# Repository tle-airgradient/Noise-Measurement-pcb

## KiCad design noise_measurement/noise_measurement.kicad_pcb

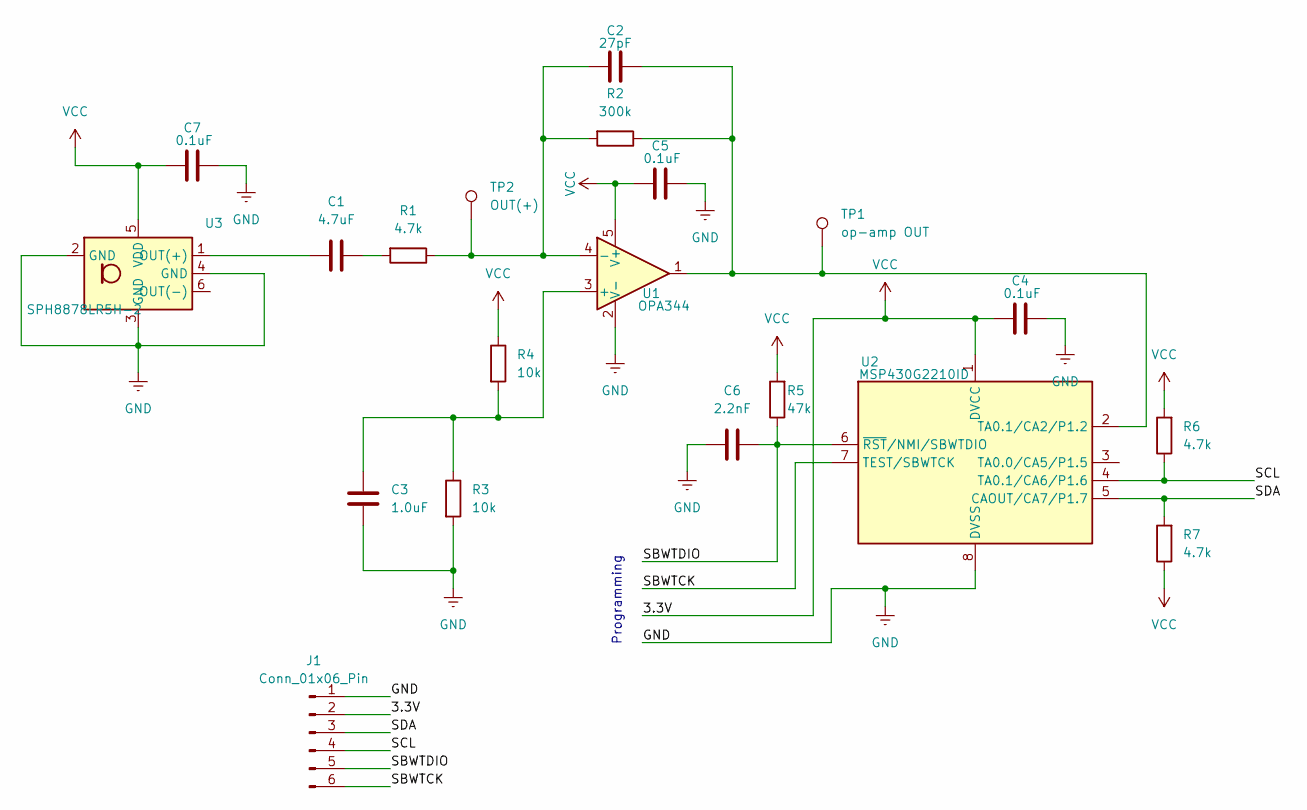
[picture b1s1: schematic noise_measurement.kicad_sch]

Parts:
C1: 4.7uF; C_0402_1005Metric
C2: 27pF; C_0402_1005Metric
C3: 1.0uF; C_0402_1005Metric
C4, C5, C7: 0.1uF; C_0402_1005Metric
C6: 2.2nF; C_0402_1005Metric
J1: Conn_01x06_Pin; PinHeader_1x06_P1.27mm_Vertical
R1, R6, R7: 4.7k; R_0402_1005Metric
R2: 300k; R_0402_1005Metric
R3, R4: 10k; R_0402_1005Metric
R5: 47k; R_0402_1005Metric
TP1: op-amp OUT; TestPoint_Pad_D1.0mm
TP2: OUT(+); TestPoint_Pad_D1.0mm
U1: OPA344; SOT-23-5
U2: MSP430G2210ID; SOIC-8_3.9x4.9mm_P1.27mm
U3: SPH8878LR5H-2; SPH8878

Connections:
/SBWTCK: J1.6, U2.7 (TEST/SBWTCK)
/SBWTDIO: C6.2, J1.5, R5.1, U2.6 (~RST/NMI/SBWTDIO)
/SCL: J1.4, R6.1, U2.4 (TA0.1/CA6/P1.6)
/SDA: J1.3, R7.2, U2.5 (CAOUT/CA7/P1.7)
GND: C3.2, C4.1, C5.1, C6.1, C7.1, J1.1, R3.2, U1.2 (V-), U2.8 (DVSS), U3.2 (GND), U3.3 (GND), U3.4 (GND)
unnamed: C1.1, R1.2
unnamed: C3.1, R3.1, R4.2, U1.3 (+)
unnamed: C2.2, R1.1, R2.2, TP2.1 (1_1), U1.4 (-)
unnamed: C2.1, R2.1, TP1.1 (1_1), U1.1, U2.2 (TA0.1/CA2/P1.2)
unnamed: C1.2, U3.1 (OUT(+))
VCC: C4.2, C5.2, C7.2, J1.2, R4.1, R5.2, R6.2, R7.1, U1.5 (V+), U2.1 (DVCC), U3.5 (VDD)

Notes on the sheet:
Programming

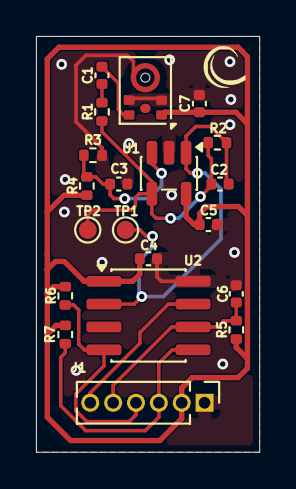
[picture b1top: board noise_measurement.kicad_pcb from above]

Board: 2 copper layers, 12.4 x 23.1 mm, 20 parts (0 on the bottom side), 11 nets.
